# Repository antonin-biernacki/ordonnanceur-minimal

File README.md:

# Ordonnanceur minimal pour ATmega328P

Ordonnanceur écrit en C pour un microcontrôleur **ATmega328P** (Arduino Uno, 16 MHz), accompagné d'un shield Arduino conçu sous **KiCad**.

Plusieurs tâches s'exécutent « en parallèle » sur un seul cœur : un timer déclenche toutes les millisecondes un changement de contexte, qui sauvegarde les registres de la tâche courante et restaure ceux de la suivante (*round-robin*).

## Sommaire

- [Contexte](#contexte)
- [Aperçu](#aperçu)
- [Fonctionnalités](#fonctionnalités)
- [Structure du projet](#structure-du-projet)
- [Matériel](#matériel)
- [Compilation et téléversement](#compilation-et-téléversement)
- [Utilisation](#utilisation)
- [Fonctionnement interne](#fonctionnement-interne)
- [Limites](#limites)
- [Crédits](#crédits)

## Contexte

Le shield, branché sur l'Arduino Uno, joue le rôle de « carte mère » : il sert à tester l'ordonnanceur, qui tourne sur l'ATmega328P de l'Arduino.

Le shield et l'ordonnanceur sont terminés et testés : LEDs, lecteur de carte SD, communication série et SPI.

## Aperçu

### Schématique

### Routage

### Démonstration

[▶ Vidéo de démonstration](docs/demo.mp4) : lancement et arrêt des tâches (LEDs et afficheur 7 segments) depuis le terminal série.

## Fonctionnalités

- Changement de contexte déclenché par l'interruption du timer 1 (quantum de 1 ms)
- Création, suppression et fin de tâches à l'exécution (`add`, `kill`, `finish`)
- Mise en veille d'une tâche pendant une durée en millisecondes (`wait`)
- Une tâche d'interface série qui permet de lancer et d'arrêter les autres tâches depuis un terminal
- Tâches de démonstration : 5 LEDs clignotant à des rythmes différents et un afficheur 7 segments piloté en SPI

## Structure du projet

```text
.
├── docs/
│   ├── schematique.png        # Schématique du shield
│   ├── routage.png            # Routage du shield
│   └── demo.mp4               # Vidéo de démonstration
├── hardware/
│   ├── SE4-shield.kicad_pro   # Projet KiCad
│   ├── SE4-shield.kicad_sch   # Schéma
│   └── SE4-shield.kicad_pcb   # Circuit imprimé
└── software/
    ├── ordonnanceur.c         # Ordonnanceur, tâches de démonstration, main
    ├── ordonnanceur.h         # Constantes, structure des tâches, macros de contexte
    ├── test.c                 # Programme de test autonome de l'afficheur 7 segments (SPI)
    └── Makefile
```

## Matériel

Le dossier `hardware/` contient un shield pour Arduino Uno R3, créé à partir du modèle de shield fourni avec KiCad : 5 LEDs avec leurs résistances, un lecteur de carte micro SD, un buffer 74LVC125 et des connecteurs pour modules SPI (lignes `CS`, `INT` et `RST` dédiées).

Le logiciel pilote en SPI un afficheur 7 segments SparkFun. Affectation des broches utilisées :

| Élément                    | Broche |
|----------------------------|--------|
| LED 1                      | PC0    |
| LED 2                      | PC3    |
| LED 3                      | PB0    |
| LED 4                      | PD4    |
| LED 5                      | PD7    |
| SPI MOSI                   | PB3    |
| SPI MISO                   | PB4    |
| SPI SCK                    | PB5    |
| Afficheur 7 segments (CS4) | PB0    |

## Compilation et téléversement

Depuis le dossier `software/` :

```bash
make          # produit ordonnanceur.hex
make flash    # téléverse sur la carte
make clean    # supprime les fichiers .elf et .hex
```

La cible est un ATmega328P cadencé à 16 MHz. Le port série du téléversement est `/dev/ttyACM0` par défaut ; pour en changer :

```bash
make flash PORT=/dev/ttyUSB0
```

## Utilisation

Au démarrage, seule la tâche d'interface série est active. Ouvrez un terminal série sur la carte (par exemple avec `minicom` ou `screen`) avec les paramètres **9600 bauds, 8 bits de données, pas de parité, 2 bits de stop** :

```bash
minicom -D /dev/ttyACM0 -b 9600
```

Chaque caractère reçu est interprété comme une commande, puis renvoyé en écho :

| Caractère | Action                                 |
|-----------|----------------------------------------|
| `1` à `5` | Lancer le clignotement de la LED 1 à 5 |
| `6`       | Arrêter la LED 1                       |
| `7`       | Arrêter la LED 2                       |
| `8`       | Arrêter la LED 3                       |
| `9`       | Arrêter la LED 4                       |
| `0`       | Arrêter la LED 5                       |
| `s`       | Lancer l'affichage 7 segments          |
| `d`       | Arrêter l'affichage 7 segments         |

## Fonctionnement interne

- **Timer** : le timer 1 est configuré en mode CTC avec un diviseur de 8 et une période de 1 ms. Son interruption (`TIMER1_COMPA_vect`) est le point d'entrée de l'ordonnanceur.
- **Table des tâches** : `Tasks_list` contient, pour chaque tâche, le pointeur de pile sauvegardé, l'adresse de la fonction, le temps de veille restant et l'état (`RUN` ou `ENDED`).
- **Changement de contexte** : l'interruption est déclarée `naked`. Les macros `SAVE_REGISTERS()` et `RESTORE_REGISTERS()` empilent et dépilent `r0` à `r31` ainsi que `SREG`, et le pointeur de pile `SP` est échangé entre deux tâches.
- **Choix de la tâche suivante** : `scheduler()` décrémente les temps de veille, puis parcourt la table en ignorant les tâches en veille ou terminées.
- **Piles** : chaque tâche dispose de sa propre pile de 100 octets, placée à partir de l'adresse `0x800` et décalée de 100 octets par tâche. Une nouvelle tâche reçoit une pile pré-remplie (adresse de départ et registres) pour qu'un retour d'interruption la démarre directement.
- **Appels bloquants** : `wait()` et `finish()` déclenchent immédiatement un changement de contexte en appelant la routine d'interruption, sans attendre le prochain tick.

## Limites

- 15 tâches au maximum (`NBTASKS`), dont la tâche d'interface série
- 100 octets de pile par tâche (`STACK_LENGTH`), dont environ 35 sont consommés par la sauvegarde du contexte
- Durée maximale de `wait()` : 32 000 ms (entier 16 bits)
- Les délais `_delay_ms` des tâches sont ralentis par les changements de contexte : le clignotement réel est plus lent que le délai demandé, d'autant plus qu'il y a de tâches actives
- La tâche série attend les caractères en boucle : un caractère reçu pendant qu'elle n'est pas en cours d'exécution risque d'être perdu
- Pas de gestion de priorités

## Crédits

- Thomas Delobelle

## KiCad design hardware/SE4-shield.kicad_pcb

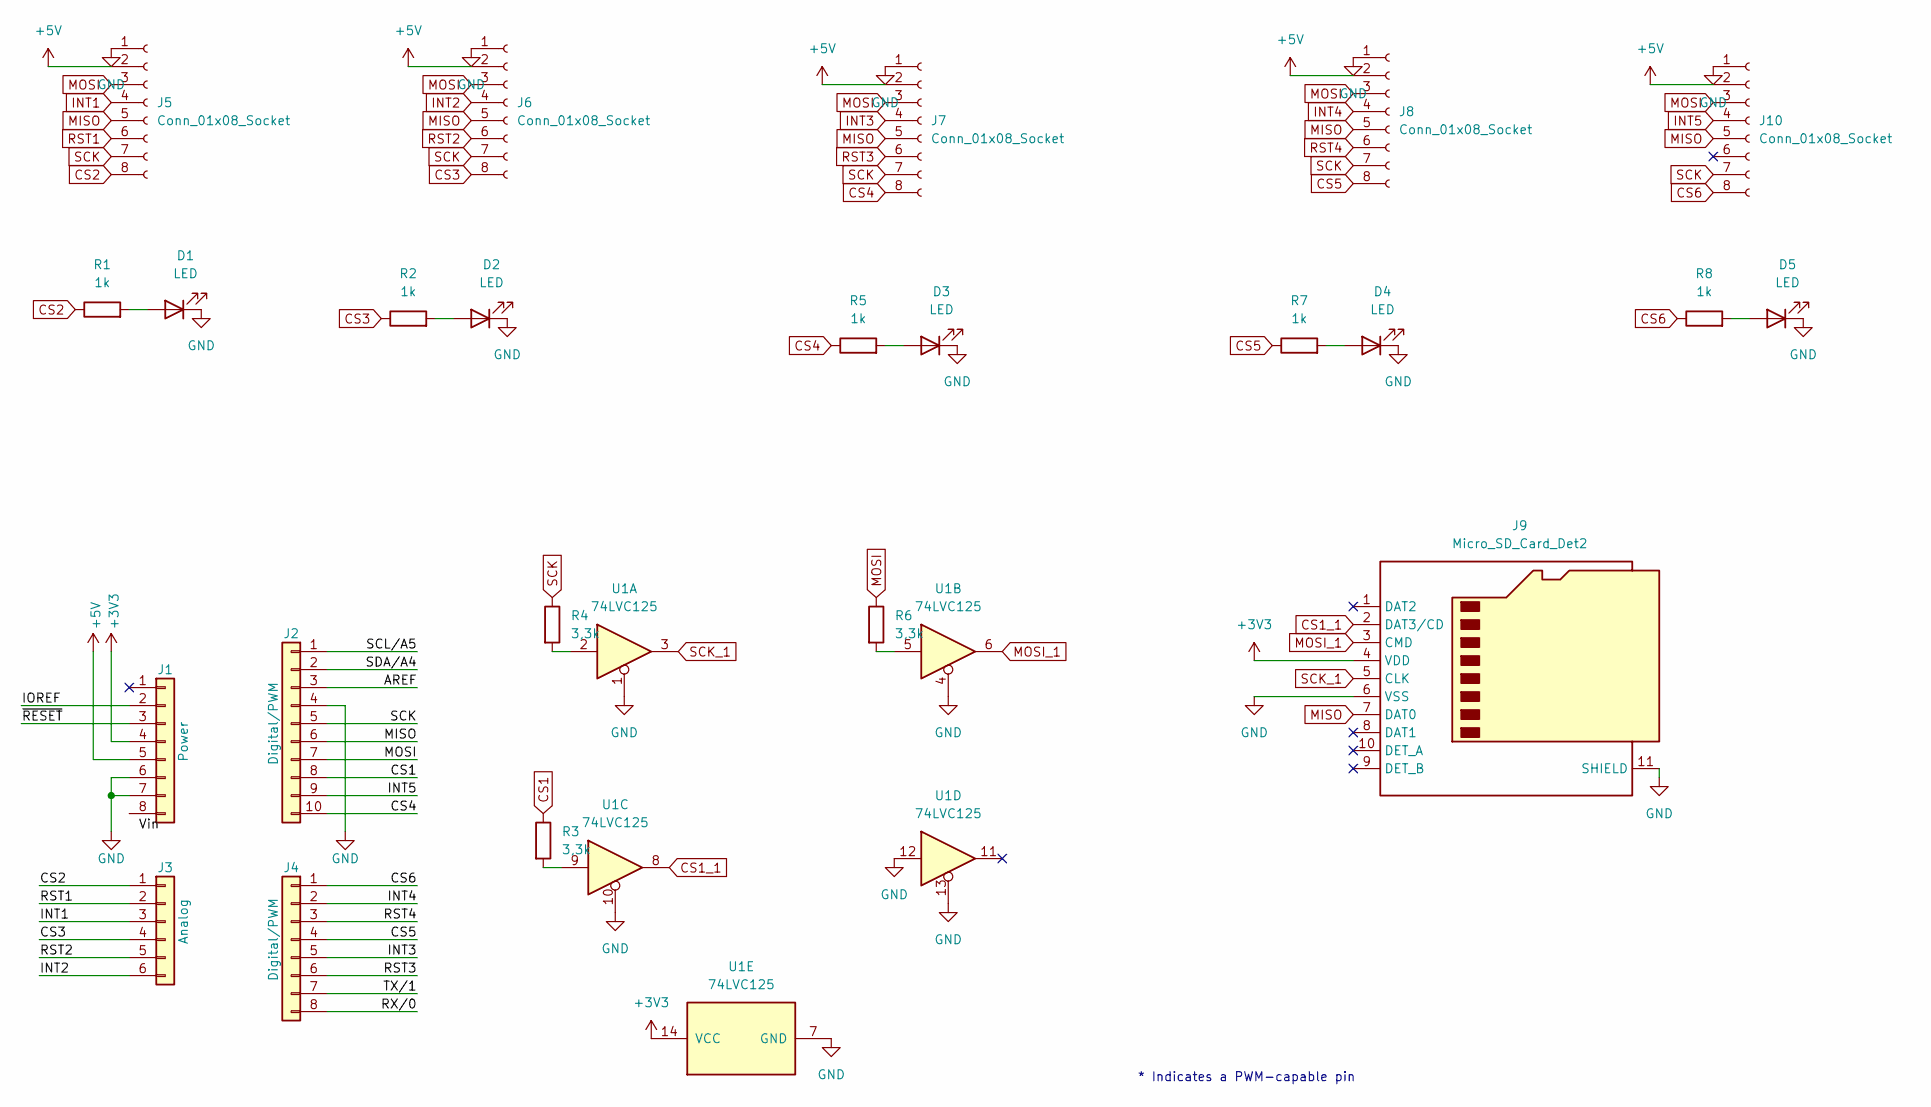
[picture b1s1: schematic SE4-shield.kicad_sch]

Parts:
D1, D2, D3, D4, D5: LED; LED_0603_1608Metric_Pad1.05x0.95mm_HandSolder
J1: Power; PinSocket_1x08_P2.54mm_Vertical
J2: Digital/PWM; PinSocket_1x10_P2.54mm_Vertical
J3: Analog; PinSocket_1x06_P2.54mm_Vertical
J4: Digital/PWM; PinSocket_1x08_P2.54mm_Vertical
J5, J6, J7, J8, J10: Conn_01x08_Socket; PinSocket_1x08_P2.54mm_Vertical
J9: Micro_SD_Card_Det2; microSD_HC_Molex_104031-0811
R1, R2, R5, R7, R8: 1k; R_0603_1608Metric_Pad0.98x0.95mm_HandSolder
R3, R4, R6: 3,3k; R_0603_1608Metric_Pad0.98x0.95mm_HandSolder
U1: 74LVC125; SOIC-14_3.9x8.7mm_P1.27mm

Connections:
+3V3: J1.4, J9.4 (VDD), U1.14 (VCC)
+5V: J1.5, J5.2, J6.2, J7.2, J8.2, J10.2
/AREF: J2.3
/IOREF: J1.2
/RX/0: J4.8
/SCL/A5: J2.1
/SDA/A4: J2.2
/TX/1: J4.7
/~RESET: J1.3
CS1: J2.8, R3.1
CS1_1: J9.2 (DAT3/CD), U1.8
CS2: J3.1, J5.8, R1.1
CS3: J3.4, J6.8, R2.1
CS4: J2.10, J7.8, R5.1
CS5: J4.4, J8.8, R7.1
CS6: J4.1, J10.8, R8.1
GND: D1.1 (K), D2.1 (K), D3.1 (K), D4.1 (K), D5.1 (K), J1.6, J1.7, J2.4, J5.1, J6.1, J7.1, J8.1, J9.6 (VSS), J9.11 (SHIELD), J10.1, U1.1, U1.4, U1.7 (GND), U1.10, U1.12, U1.13
INT1: J3.3, J5.4
INT2: J3.6, J6.4
INT3: J4.5, J7.4
INT4: J4.2, J8.4
INT5: J2.9, J10.4
MISO: J2.6, J5.5, J6.5, J7.5, J8.5, J9.7 (DAT0), J10.5
MOSI: J2.7, J5.3, J6.3, J7.3, J8.3, J10.3, R6.1
MOSI_1: J9.3 (CMD), U1.6
unnamed: D1.2 (A), R1.2
unnamed: D2.2 (A), R2.2
unnamed: D3.2 (A), R5.2
unnamed: D4.2 (A), R7.2
unnamed: D5.2 (A), R8.2
unnamed: R3.2, U1.9
unnamed: R4.2, U1.2
unnamed: R6.2, U1.5
RST1: J3.2, J5.6
RST2: J3.5, J6.6
RST3: J4.6, J7.6
RST4: J4.3, J8.6
SCK: J2.5, J5.7, J6.7, J7.7, J8.7, J10.7, R4.1
SCK_1: J9.5 (CLK), U1.3

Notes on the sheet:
* Indicates a PWM-capable pin

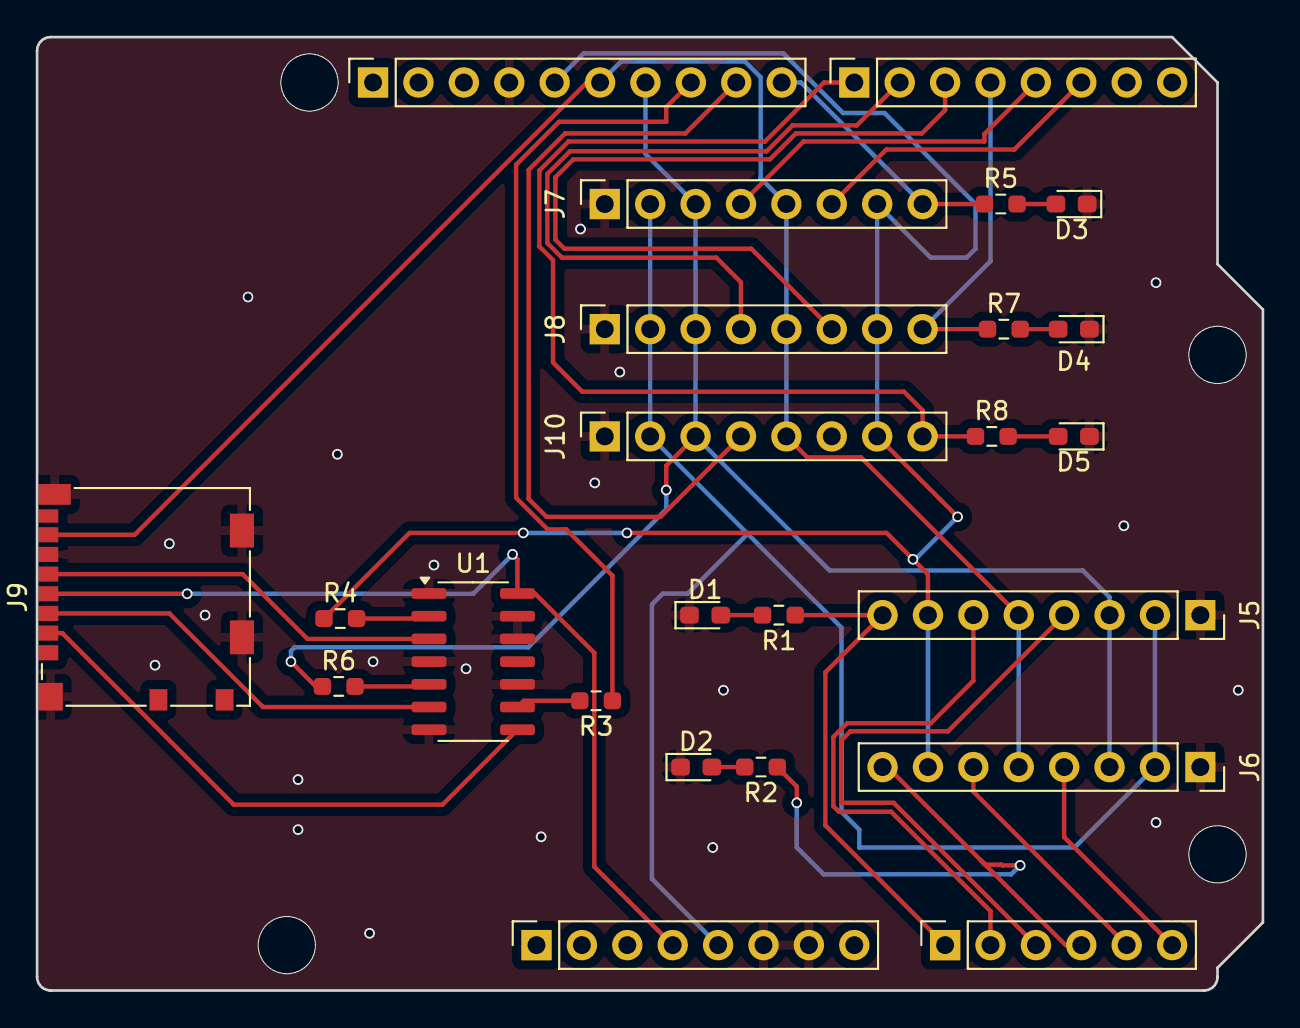
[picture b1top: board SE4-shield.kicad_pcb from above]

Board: 2 copper layers, 68.6 x 53.3 mm, 28 parts (0 on the bottom side), 32 nets.

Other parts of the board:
MH1, MH2, MH3, MH4: MountingHole_3.2mm
